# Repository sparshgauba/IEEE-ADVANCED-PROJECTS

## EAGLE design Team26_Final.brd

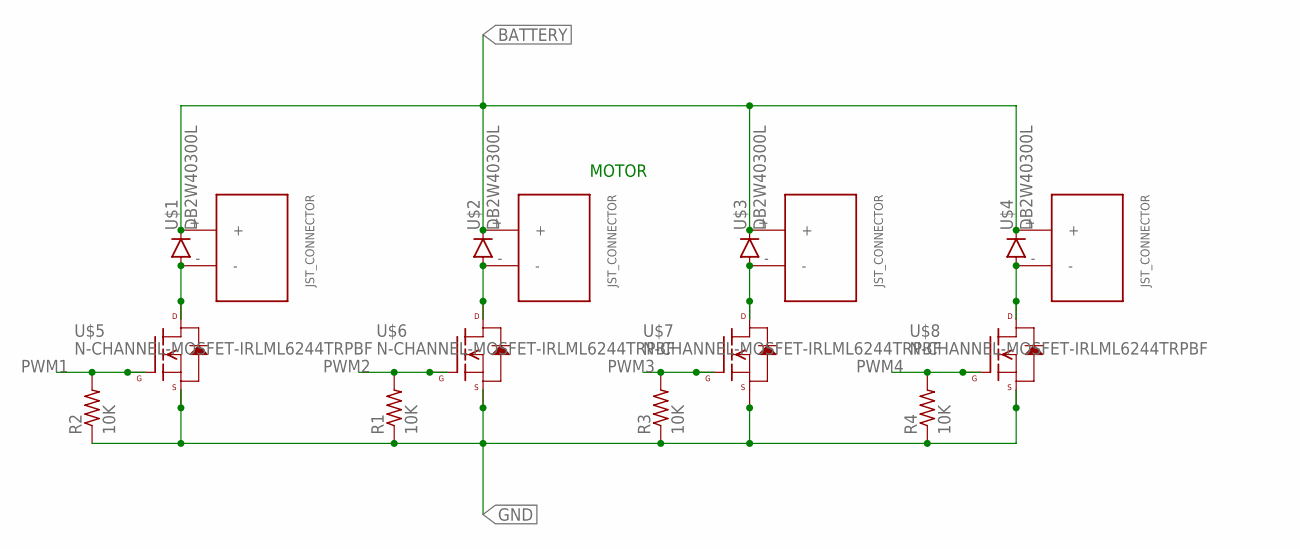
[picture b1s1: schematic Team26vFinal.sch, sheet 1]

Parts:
MOTOR, MOTOR1, MOTOR2, MOTOR3: JST_CONNECTOR_FEMALE
R1, R2, R3, R4: 10K; R0603
U$1, U$2, U$3, U$4: DB2W40300L; MINI2-F3-B
U$5, U$6, U$7, U$8: N-CHANNEL-MOSFET-IRLML6244TRPBF; SOT23-3

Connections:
BATTERY: MOTOR.+, MOTOR1.+, MOTOR2.+, MOTOR3.+, U$1.NEG (GPIN), U$2.NEG (GPIN), U$3.NEG (GPIN), U$4.NEG (GPIN); also elsewhere on the board
GND: R1.1, R2.1, R3.1, R4.1, U$5.2 (S), U$6.2 (S), U$7.2 (S), U$8.2 (S); also elsewhere on the board
unnamed: MOTOR.-, U$2.POS (PPIN), U$6.3 (D)
unnamed: MOTOR1.-, U$1.POS (PPIN), U$5.3 (D)
unnamed: MOTOR2.-, U$3.POS (PPIN), U$7.3 (D)
unnamed: MOTOR3.-, U$4.POS (PPIN), U$8.3 (D)
PWM1: R2.2, U$5.1 (G); also elsewhere on the board
PWM2: R1.2, U$6.1 (G); also elsewhere on the board
PWM3: R3.2, U$7.1 (G); also elsewhere on the board
PWM4: R4.2, U$8.1 (G); also elsewhere on the board

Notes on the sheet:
MOTOR

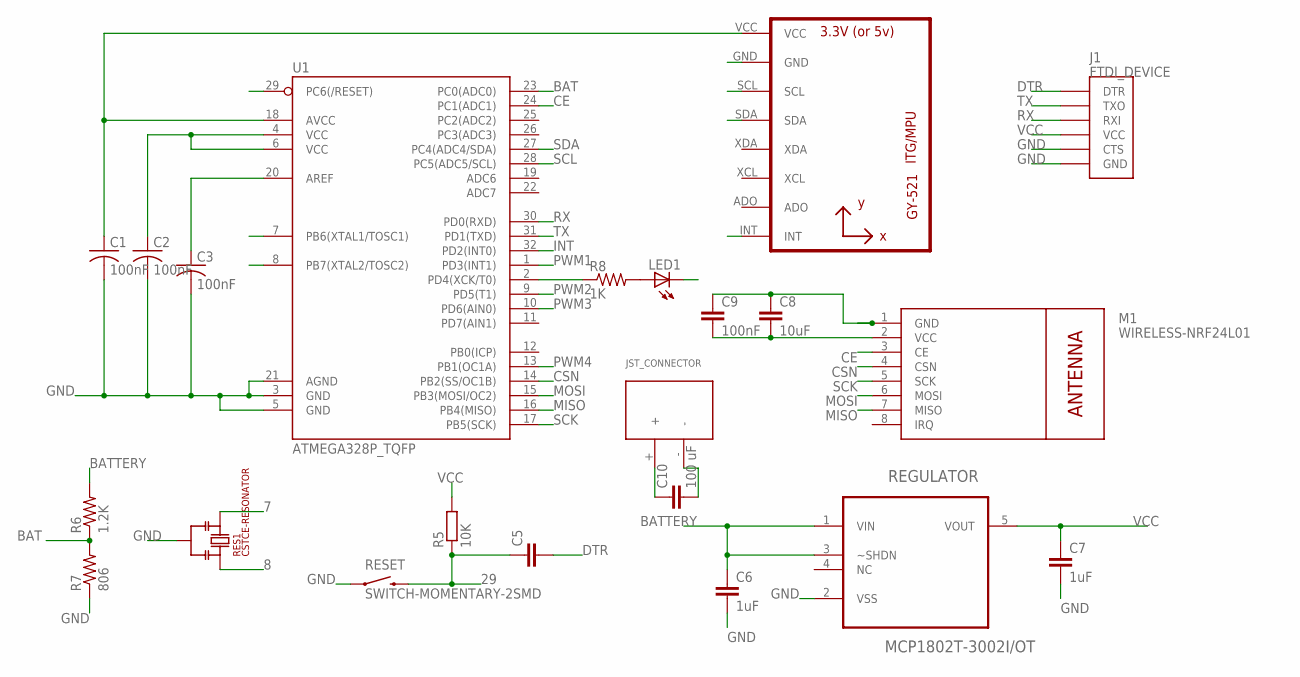
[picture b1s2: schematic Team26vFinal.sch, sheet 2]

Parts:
C1, C2, C3, C9: 100nF; C0603
C5: C-EUC0603; C0603
C6, C7: 1uF; C0603
C8: 10uF; C0603
C10: 100 uF; C1210
J1: FTDI_DEVICE; FTDI_DEVICE_SIDE
LED1: LEDCHIP-LED0603; CHIP-LED0603
M1: WIRELESS-NRF24L01
R5: 10K; R0603
R6: 1.2K; R0603
R7: 806; R0603
R8: 1K; R0603
REGULATOR: MCP1802T-3002I/OT; SOT95P270X145-5N
RES1: CSTCE-RESONATOR; CSTCE16M0V53-R0
RESET: SWITCH-MOMENTARY-2SMD; TACTILE-SWITCH-SMD
U1: ATMEGA328P_TQFP; TQFP32-08
U2: GY-521MPU6050; GY-521
U$9: JST_CONNECTOR_FEMALE

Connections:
7: RES1.P$3, U1.7 (PB6(XTAL1/TOSC1))
8: RES1.P$1, U1.8 (PB7(XTAL2/TOSC2))
29: C5.1, R5.1, RESET.3 (2), U1.29 (PC6(/RESET))
BAT: R6.1, R7.2, U1.23 (PC0(ADC0))
BATTERY: C6.1, C10.1, R6.2, REGULATOR.1 (VIN), REGULATOR.3 (~SHDN), U$9.+; also elsewhere on the board
CE: M1.3 (CE), U1.24 (PC1(ADC1))
CSN: M1.4 (CSN), U1.14 (PB2(SS/OC1B))
DTR: C5.2, J1.P$1 (DTR)
GND: C1.2, C2.2, C3.2, C6.2, C7.2, C8.1, C9.1, C10.2, J1.P$5 (CTS), J1.P$6 (GND), LED1.C, M1.1 (GND), R7.1, REGULATOR.2 (VSS), RES1.P$2, RESET.1, U1.3 (GND), U1.5 (GND), U1.21 (AGND), U2.GND, U$9.-; also elsewhere on the board
INT: U1.32 (PD2(INT0)), U2.INT
MISO: M1.7 (MISO), U1.16 (PB4(MISO))
MOSI: M1.6 (MOSI), U1.15 (PB3(MOSI/OC2))
unnamed: LED1.A, R8.2
unnamed: C3.1, U1.20 (AREF)
unnamed: R8.1, U1.2 (PD4(XCK/T0))
PWM1: U1.1 (PD3(INT1)); also elsewhere on the board
PWM2: U1.9 (PD5(T1)); also elsewhere on the board
PWM3: U1.10 (PD6(AIN0)); also elsewhere on the board
PWM4: U1.13 (PB1(OC1A)); also elsewhere on the board
RX: J1.P$3 (RXI), U1.30 (PD0(RXD))
SCK: M1.5 (SCK), U1.17 (PB5(SCK))
SCL: U1.28 (PC5(ADC5/SCL)), U2.SCL
SDA: U1.27 (PC4(ADC4/SDA)), U2.SDA
TX: J1.P$2 (TXO), U1.31 (PD1(TXD))
VCC: C1.1, C2.1, C7.1, C8.2, C9.2, J1.P$4 (VCC), M1.2 (VCC), R5.2, REGULATOR.5 (VOUT), U1.4 (VCC), U1.6 (VCC), U1.18 (AVCC), U2.VCC

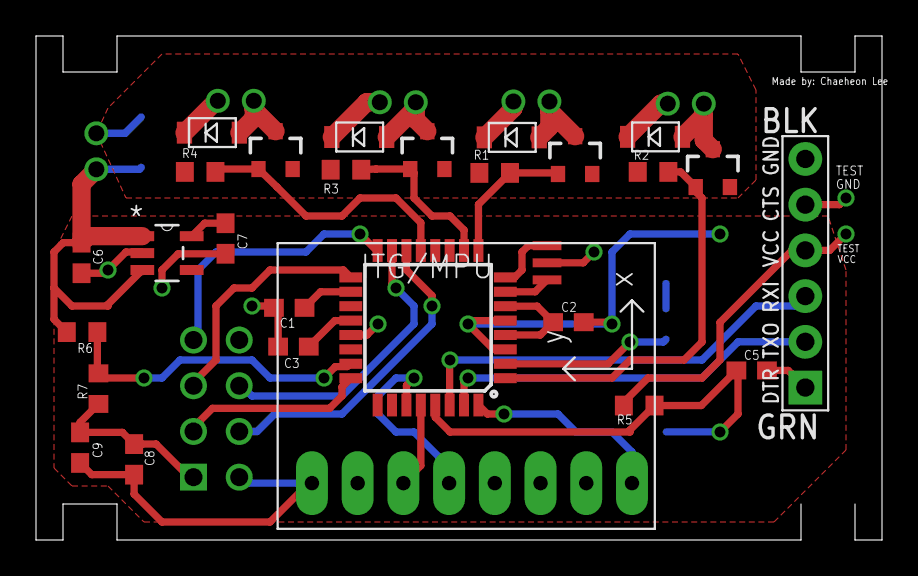
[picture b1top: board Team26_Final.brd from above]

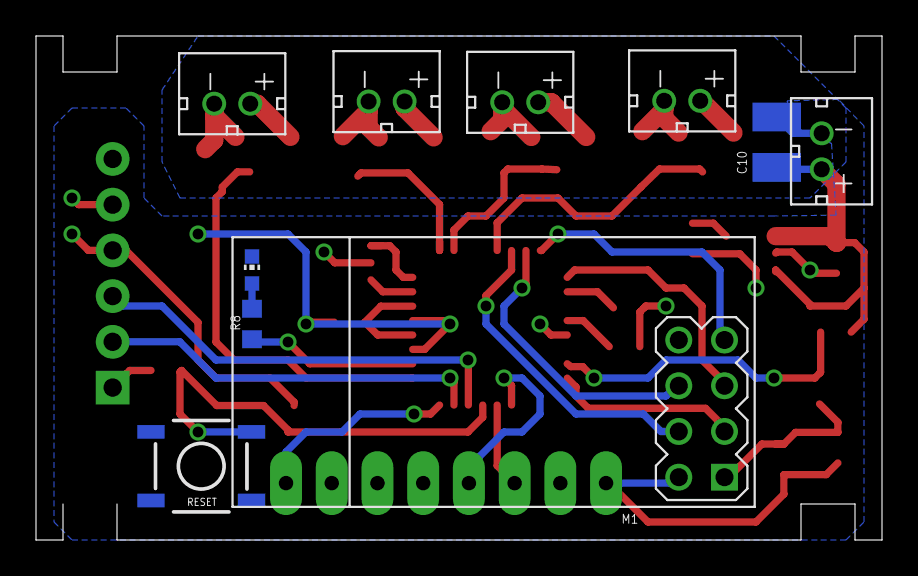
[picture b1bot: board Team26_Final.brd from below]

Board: 2 copper layers, 47.0 x 28.0 mm, 38 parts (10 on the bottom side), 29 nets.

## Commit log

2018-06-02 Sauce
2018-06-03 Gyro Added
2018-06-03 New sensor library
